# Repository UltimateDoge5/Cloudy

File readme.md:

# Cloudy

A weather station with a fronted UI and PHP backend was my first-ever web project.
It has been 4 years since I finished it, and I've decided to do it again but with my current knowledge.

Another reason for this project is that I wanted to learn how to design schematics and PCBs.
You can see the (hopefully) live data on the [website](https://cloudy.pkozak.org).

## Hardware

The station uses a BME280 sensor to measure temperature, humidity and pressure.

The [schematics](/schematics/) and PCB use an ESP32-C3-MINI-N4,
but because of the costs of manufacturing, assembly/stencil and shipping,
I've decided to assemble it on a breadboard with an ESP32-WROOM devkit for now.

The [schematics](/schematics/) also include a 3.3V voltage regulator, USB type C for power and programming,
and an IDC header for a PMS7003 air quality sensor that I plant to integrate later.

As for the future sensors, aside from the PM2.5 sensor, I'd like to add a rain sensor and an anemometer.
The first one is cheap and easy to do, but the second one is not so much.
Anemometers are expensive, and I don't have the tools to make one myself.
Even if I had one, I do not have an appropriate location to install it.

## Software

The software for the station is in the [driver folder](./driver).
It's written in C++ and uses Arduino libraries.
For the backend, I've decided to use Supabase,
because of the REST database API and the real-time features which allowed an easy integration with the microcontroller.

## Issues/Caveats

-   One issue is that I don't have a fully shaded place to put the sensor.
    That results in ridiculously high temperature
    readings when the sun is shining on it.
    I'm working on a solution for that.
-   Air quality sensors operate on 5V, and it's not a problem while on USB power.
    The battery voltage is regulated to 3.3V.
    So adding a dedicated 5V boost converter is not really sensible and inefficient,
    so while working off the battery, the air quality sensor will be turned off.

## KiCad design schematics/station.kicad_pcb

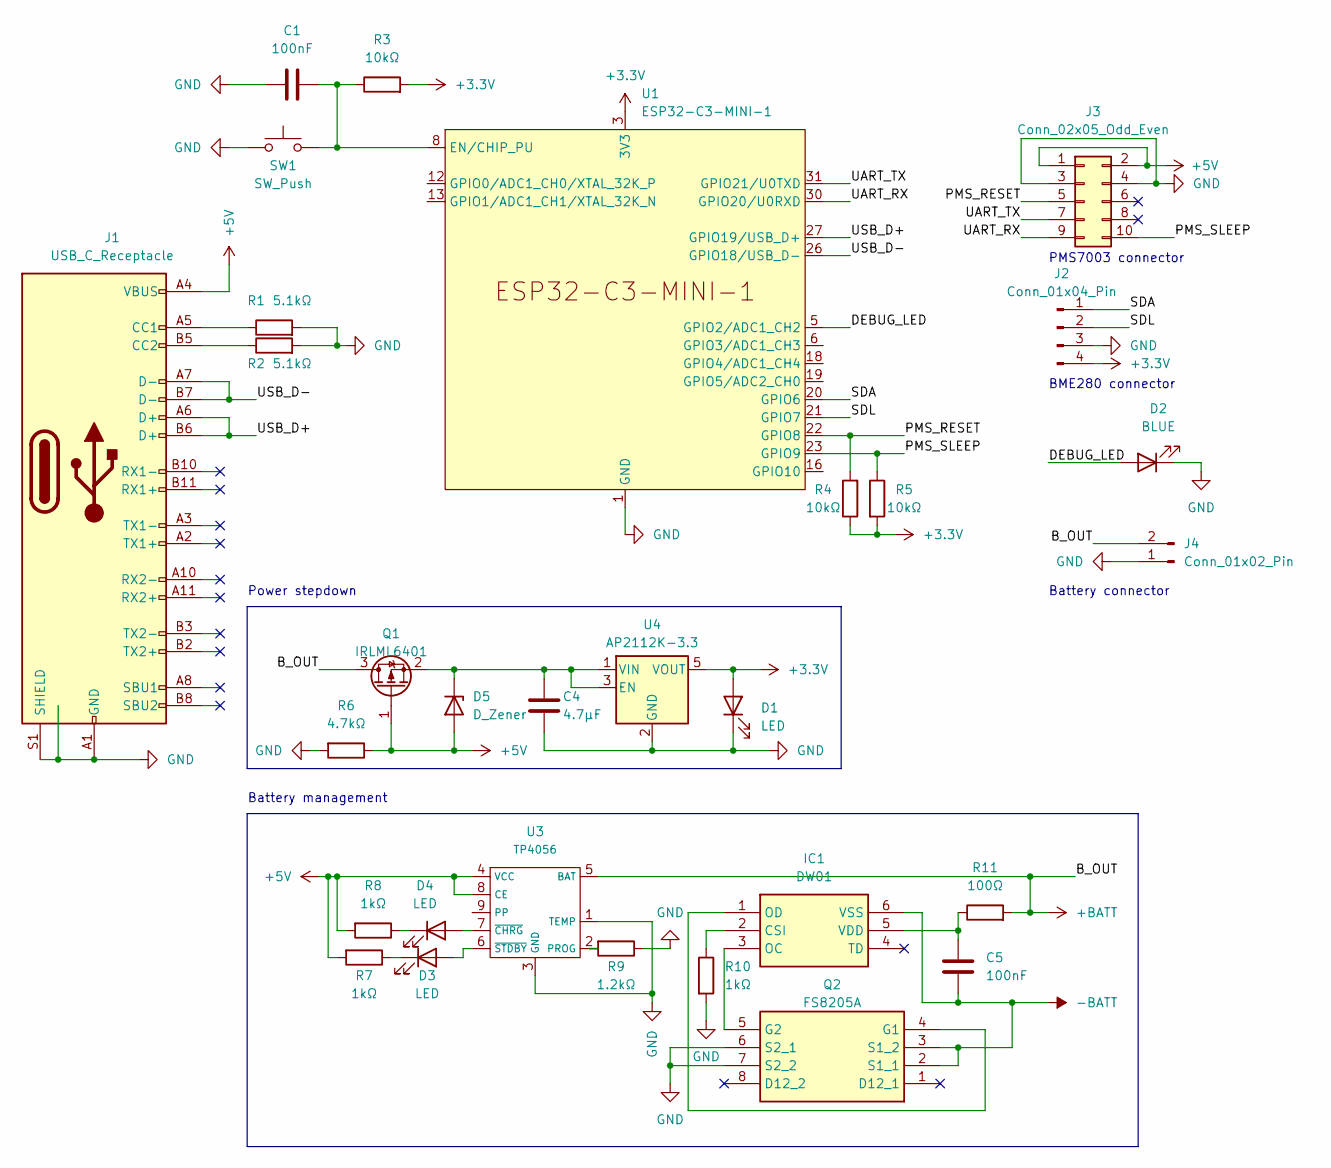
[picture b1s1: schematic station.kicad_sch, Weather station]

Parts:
C1, C5: 100nF; C_0805_2012Metric_Pad1.18x1.45mm_HandSolder
C4: 4.7µF; C_0805_2012Metric_Pad1.18x1.45mm_HandSolder
D1, D3, D4: LED; LED_1812_4532Metric_Pad1.30x3.40mm_HandSolder
D2: BLUE; LED_0805_2012Metric_Pad1.15x1.40mm_HandSolder
D5: D_Zener; D_SMA_Handsoldering
IC1: DW01; SOT95P280X135-6N; Manufacturer_Part_Number DW01
J1: USB_C_Receptacle; USB_C_Receptacle_Amphenol_12401610E4-2A
J2: Conn_01x04_Pin; PinHeader_1x04_P2.54mm_Vertical
J3: Conn_02x05_Odd_Even; IDC-Header_2x05_P2.54mm_Vertical
J4: Conn_01x02_Pin; JST_ACH_BM02B-ACHSS-GAN-ETF_1x02-1MP_P1.20mm_Vertical
Q1: IRLML6401; SOT-23
Q2: FS8205A; SOP65P640X120-8N; Manufacturer_Part_Number FS8205A
R1, R2: 5.1kΩ; R_1206_3216Metric
R3, R4, R5: 10kΩ; R_1206_3216Metric
R6: 4.7kΩ; R_1206_3216Metric
R7, R8, R10: 1kΩ; R_1206_3216Metric
R9: 1.2kΩ; R_1206_3216Metric
R11: 100Ω; R_1206_3216Metric
SW1: SW_Push; SW_PUSH_6mm_H5mm
U1: ESP32-C3-MINI-1
U3: TP4056; SOIC-8-1EP_3.9x4.9mm_P1.27mm_EP2.29x3mm
U4: AP2112K-3.3; SOT-23-5

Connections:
+3.3V: D1.2 (A), J2.4, R3.2, R4.1, R5.2, U1.3 (3V3), U4.5 (VOUT)
+5V: D5.2 (A), J1.A4 (VBUS), J1.A9 (VBUS), J1.B4 (VBUS), J1.B9 (VBUS), J3.1, J3.2, Q1.1 (G), R6.1, R7.2, R8.2, U3.4 (VCC), U3.8 (CE)
+BATT: J4.2, Q1.3 (D), R11.2, U3.5 (BAT)
-BATT: C5.2, IC1.6 (VSS), Q2.2 (S1_1), Q2.3 (S1_2)
/DEBUG_LED: D2.2 (A), U1.5 (GPIO2/ADC1_CH2)
/PMS_RESET: J3.5, R4.2, U1.22 (GPIO8)
/PMS_SLEEP: J3.10, R5.1, U1.23 (GPIO9)
/SDA: J2.1, U1.20 (GPIO6)
/SDL: J2.2, U1.21 (GPIO7)
/UART_RX: J3.9, U1.30 (GPIO20/U0RXD)
/UART_TX: J3.7, U1.31 (GPIO21/U0TXD)
/USB_D+: J1.A6 (D+), J1.B6 (D+), U1.27 (GPIO19/USB_D+)
/USB_D-: J1.A7 (D-), J1.B7 (D-), U1.26 (GPIO18/USB_D-)
GND: C1.1, C4.2, D1.1 (K), D2.1 (K), J1.A1 (GND), J1.A12 (GND), J1.B1 (GND), J1.B12 (GND), J1.S1 (SHIELD), J2.3, J3.3, J3.4, J4.1, Q2.6 (S2_1), Q2.7 (S2_2), R1.2, R2.2, R6.2, R9.1, R10.2, SW1.1, U1.1 (GND), U1.2 (GND), U1.11 (GND), U1.14 (GND), U1.36 (GND), U1.37 (GND), U1.38 (GND), U1.39 (GND), U1.40 (GND), U1.41 (GND), U1.42 (GND), U1.43 (GND), U1.44 (GND), U1.45 (GND), U1.46 (GND), U1.47 (GND), U1.48 (GND), U1.49 (GND), U1.50 (GND), U1.51 (GND), U1.52 (GND), U1.53 (GND), U3.1 (TEMP), U3.3 (GND), U4.2 (GND)
unnamed: D3.2 (A), U3.6 (~STDBY)
unnamed: D3.1 (K), R7.1
unnamed: D4.2 (A), U3.7 (~CHRG)
unnamed: D4.1 (K), R8.1
unnamed: C4.1, D5.1 (K), Q1.2 (S), U4.1 (VIN), U4.3 (EN)
unnamed: IC1.2 (CSI), R10.1
unnamed: IC1.3 (OC), Q2.5 (G2)
unnamed: IC1.1 (OD), Q2.4 (G1)
unnamed: C5.1, IC1.5 (VDD), R11.1
unnamed: J1.A5 (CC1), R1.1
unnamed: J1.B5 (CC2), R2.1
unnamed: C1.2, R3.1, SW1.2, U1.8 (EN/CHIP_PU)
unnamed: R9.2, U3.2 (PROG)

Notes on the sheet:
BME280 connector
Battery connector
Battery management
PMS7003 connector
Power stepdown

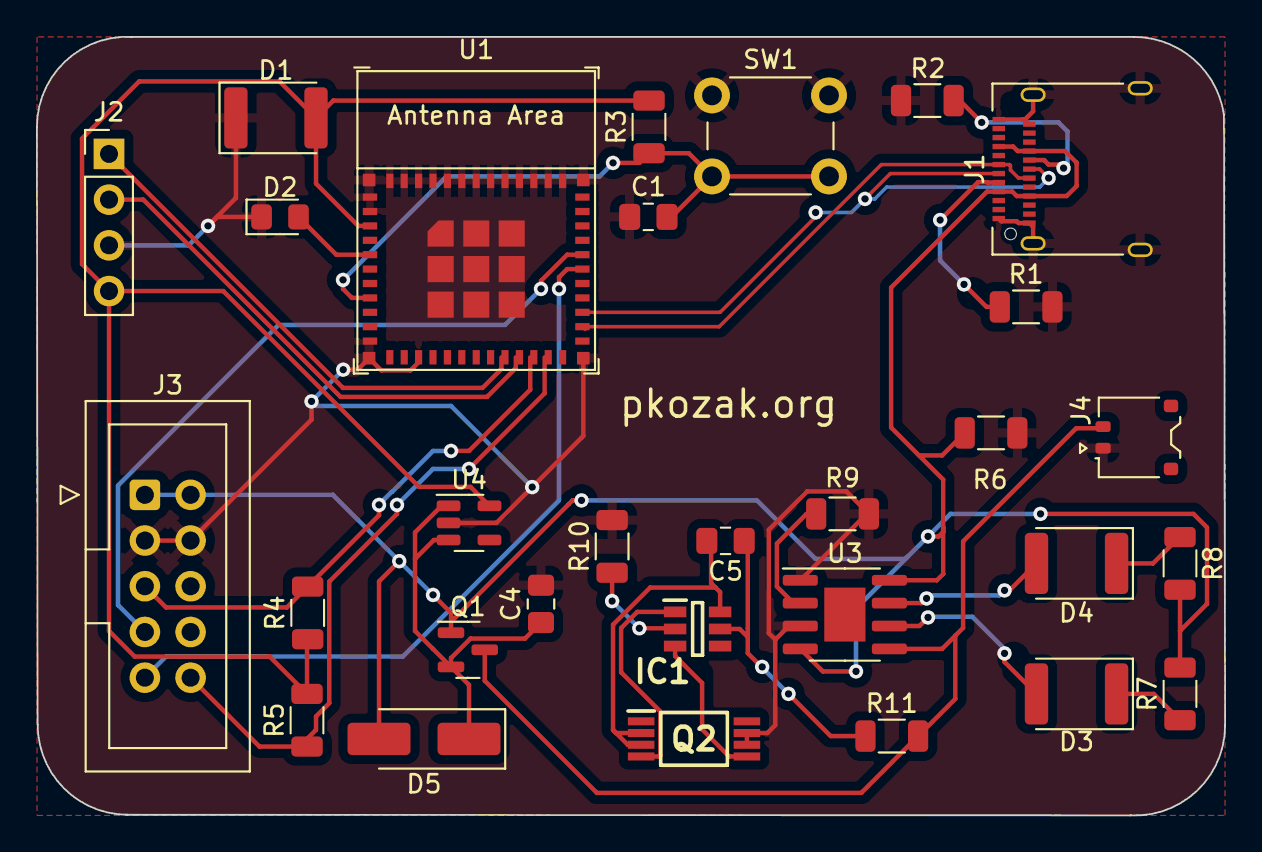
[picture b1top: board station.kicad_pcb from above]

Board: 2 copper layers, 66.0 x 43.2 mm, 30 parts (0 on the bottom side), 27 nets.

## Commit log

2022-12-06 Project init
2022-12-11 Added the charts
2022-12-21 Added the endpoint for adding data
    Added the endpoint for adding weather data to the database.
2023-02-15 Added pagination to the endpoint
    Updated schema.
2023-08-22 Finished the offline driver
2023-08-22 Driver now uploads data to db
2023-08-22 Added invalid value checks
    Added invalid value checks and a screen saver to prevent burn-in.
2023-08-23 Removed prisma
    Removed prisma and switched to pnpm
2023-08-23 Added realtime updates and new UI
2023-08-24 Added the 24 hour chart
2023-08-24 Added the uptime chart
2023-08-25 Added loading animations
2023-08-26 Added the readme
2023-08-26 Improved chart rendering times
2023-08-26 Added realtime updates to charts
2023-08-26 Fixed a bug with the timeline getting reset
2023-08-27 Added dark mode support
    Added dark mode support and the debug led to the station.
2023-08-27 Improved responsivness
    Added additional data checks to the driver
2023-08-29 Light mode text color corrections
2023-08-30 Added max and min temp display for current month
2023-08-31 Added dates to month records
2023-09-01 Gaps between records are now visualised
2023-09-02 Added the KiCad files
2023-09-02 Added another decoupling capacitor
2023-09-05 Some clarity changes and minor refactors
2023-09-13 Reorganized the grid, better responsiveness
2023-09-14 Added time gaps visualization
2023-09-17 Added gaps visualization toggle
2023-09-18 Delay between uploads now should be constant
2023-09-25 Added the month summary chart
2023-09-26 Added month selection in summary
2023-09-26 Fixed type import path
2023-09-26 Changed the styling of the month picker
    Added loading ui
2023-09-27 Added the ICs responsible for handling the battery
2023-09-28 Added avg to the month summary
    Added rainy cloud icon
2023-09-29 Changed the monthly chart tooltip format
2023-09-30 Tweaked the power source switching circuit
2023-10-01 Minor responsiveness changes
    Added a link to go back to the main page from the monthly summary.
2023-10-08 Added microcontroller reboots
2023-11-24 Fixed a bug with temperatures lower than 1.0
    Fixed a bug where temperatures lower than 1.0 would not upload.
2023-11-24 Changed icon background color
2024-03-30 Added a chart for viewing data for each day
